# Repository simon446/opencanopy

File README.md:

# OpenCanopy — Tabletop Automated Pepper Grower

Open-source, zero-config, offline-first tabletop grow unit for a single hot pepper plant.

OpenCanopy is an open-hardware project: a compact, living-room-friendly appliance that keeps one hot
pepper plant healthy indoors with minimal user involvement. It combines a broad-spectrum horticultural
LED, automated pump irrigation with soil-moisture sensing, climate/VPD monitoring, water-safety
interlocks, and a simple LED status interface — all driven by deterministic, fully local **Rust**
firmware (`no_std`, `esp-hal`) on an ESP32-S3.

📖 **Docs site:** <https://simon446.github.io/opencanopy/> · 🧩 **Contributing:** [`CONTRIBUTING.md`](CONTRIBUTING.md) · ⚖️ **Licensing:** [`LICENSES/`](LICENSES/)

The project is built **work item by work item**, organized by engineering discipline. The full
engineering plan and the per-discipline work-item breakdown live in [`plan/`](plan/) — the design
source for the build (engineering spec + work items), tracked alongside the implementation in this repo.

## Project status

- **Repository skeleton, licensing, scope lock, risk register, and CI are in place** (the Project &
  Repo track is complete) — every discipline has a home and quality gates run on each PR.
- **Firmware language: Rust** (`no_std` + `esp-hal`), with a host-testable `control` crate and
  `cargo fmt`/`clippy`/`test` gates in CI.
- The remaining discipline tracks (plant science, firmware, electronics, mechanical, validation, docs)
  follow the work-item breakdown in `plan/`. A spec design review (§23) added pre-order modeling and
  bench-characterization gates and an n=2 parallel grow trial.

## Where things live

| What | Path |
|---|---|
| Documentation (rendered) | <https://simon446.github.io/opencanopy/> |
| Documentation (source) | [`docs/`](docs/) — requirements, scope, risk register, guides |
| Contributing & workflow | [`CONTRIBUTING.md`](CONTRIBUTING.md); issue/PR templates in [`.github/`](.github/) |
| Licensing (per asset type) | [`LICENSES/`](LICENSES/) |
| Implementation subtrees | [`firmware/`](firmware/), [`electronics/`](electronics/), [`mechanical/`](mechanical/), [`validation/`](validation/), [`scripts/`](scripts/) |
| Work items & engineering spec (design source) | [`plan/`](plan/) — engineering spec + per-discipline work items |

## Scope

- **In V1:** one plant, fixed hot-pepper profile, dimmable full-spectrum LED with automated schedule,
  substrate moisture sensing, automated pump watering, reservoir-level + leak safety, temp/humidity
  sensing with VPD, circulation fan, 5-LED status interface, local deterministic firmware, and open
  hardware/firmware/CAD with simulation, hardware-in-loop, and grow-trial validation.
- **Not in V1:** camera/AI plant diagnosis, cloud control, automatic pH/EC dosing, multi-plant
  support, required mobile app, or AC mains inside the unit.

See [`docs/scope.md`](docs/scope.md) for the locked non-goals and [`docs/product-requirements.md`](docs/product-requirements.md)
for the locked physical/hardware envelope.

## Repository layout

The standard open-hardware structure is in place; each subtree has a README describing its purpose:

- `firmware/` — Rust workspace: `control/` (host-testable `no_std` logic), `controller/` (`esp-hal`
  binary), `sim/`, `hil/`.
- `electronics/` — KiCad PCB, wiring, BOM, and electrical verification.
- `mechanical/` — CAD/STEP/STL, drawings, and print settings.
- `docs/` — requirements, scope, risk register, and the guides that ship with V1.
- `validation/` — test plans, measurements, and grow-trial records.
- `scripts/` — tooling (`bom_check.py` §16.3 grow-light gate, `stl_check.py`, calculators).

Full layout: spec §14 (in `plan/`).

## Release gate

V1 is tagged only when the acceptance criteria in the V1 spec (§21, in `plan/`) are all met, as proven
by the Validation & QA track — including an **n=2 parallel grow trial** (design-review decision, §23).

## License

Per-asset open-source licensing — **Apache-2.0** firmware/scripts, **CERN-OHL-S v2** hardware/mechanical,
**CC BY 4.0** docs. See [`LICENSES/`](LICENSES/) and its [mapping note](LICENSES/README.md).

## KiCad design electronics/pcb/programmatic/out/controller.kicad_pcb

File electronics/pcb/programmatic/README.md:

<!-- SPDX-License-Identifier: CERN-OHL-S-2.0 -->
# Programmatic PCB — headless code → Gerbers (no KiCad GUI)

A **fully scripted, GUI-free** path from our schematic netlist to a routed board and a fabrication
package, using [**tscircuit**](https://tscircuit.com) (React/TSX EDA with a built-in autorouter and
Gerber export). This answers "can the PCB be built programmatically?" — **yes**, and this directory is
the working proof, generated from [`../netlist/controller_netlist.py`](../netlist/controller_netlist.py).

Built following the official [tscircuit skill](https://github.com/tscircuit/skill) idioms (named-net
connectivity, real passive elements, `pinLabels`).

## Files

| File | What |
|---|---|
| [`gen_tscircuit.py`](gen_tscircuit.py) | Generator: reads the netlist → emits the tscircuit board. |
| `controller.circuit.tsx` | Generated board (60 populated parts, 169 net connections). Do not hand-edit. |
| [`build.sh`](build.sh) | One-shot pipeline: install toolchain → generate → build → export. |
| `out/controller.gerbers.zip` | **Gerbers + drill + BOM + pick-and-place** — a complete fab package. |
| `out/controller.kicad_pcb` | The same board as a KiCad PCB (bridge back to KiCad for refinement). |
| `out/controller.pcb.png` | Rendered preview of the auto-placed/-routed board. |

## Reproduce

```sh
./build.sh          # needs node+npm, bun, network (installs @tscircuit/cli on first run)
```

## The honest status — this is a DRAFT, not a fab-ready board

The pipeline is real and the outputs are genuine fab-format files, but **don't send them to a fab as
is**:

1. **Footprints:** passive footprints (0402/0805/1206/1210/2512) are real; **IC, connector, and the
   ESP32-S3 module footprints are single-row `pinrowN` placeholders** — correct pin *count*, wrong
   land pattern. Swap in real footprints (`tsci search`/`tsci import`, or KiCad libraries) before fab.
2. **Layout quality:** auto-placement + autoroute is **autorouter-grade**. The autorouter logged
   `ran out of iterations` — routing is incomplete/rough. It honours the *netlist* but **not** the
   power/analog separation, copper-pour heatsinks, or star ground in
   [`../../analysis/design-rules.md`](../../analysis/design-rules.md). For a 24 V high-current +
   analog-moisture board, that separation is a correctness/safety concern, not cosmetics.
3. **Scope:** only **populated** controller parts are emitted (DNP options omitted; the status-LED
   board is a separate PCB). Diode anode/cathode and module pinouts on placeholder footprints need a
   review pass.

## Where this fits

This is **the** PCB route ([ECO-002](../../analysis/ECO-002-pcb-toolchain.md); KiCad retired): the
(complete, CI-checked) netlist → tscircuit → autoroute → Gerbers, no GUI. Best for fast, reproducible
drafts and CI; refine footprints/placement, then re-export.

To reach a *fabricable* board the remaining work is real footprints + a reviewed power/analog/thermal
placement per [`design-rules.md`](../../analysis/design-rules.md) — the autorouter doesn't remove that
review. If you'd rather do that refinement in KiCad, `out/controller.kicad_pcb` (and the netlist's
`controller.net`) open the design there — **optional interchange**, not required.

> Toolchain note: tscircuit (npm/bun) is **not** a repo dependency or a CI gate — it's an optional
> build tool installed on demand by `build.sh`. The plain-Python netlist ERC remains the committed gate.

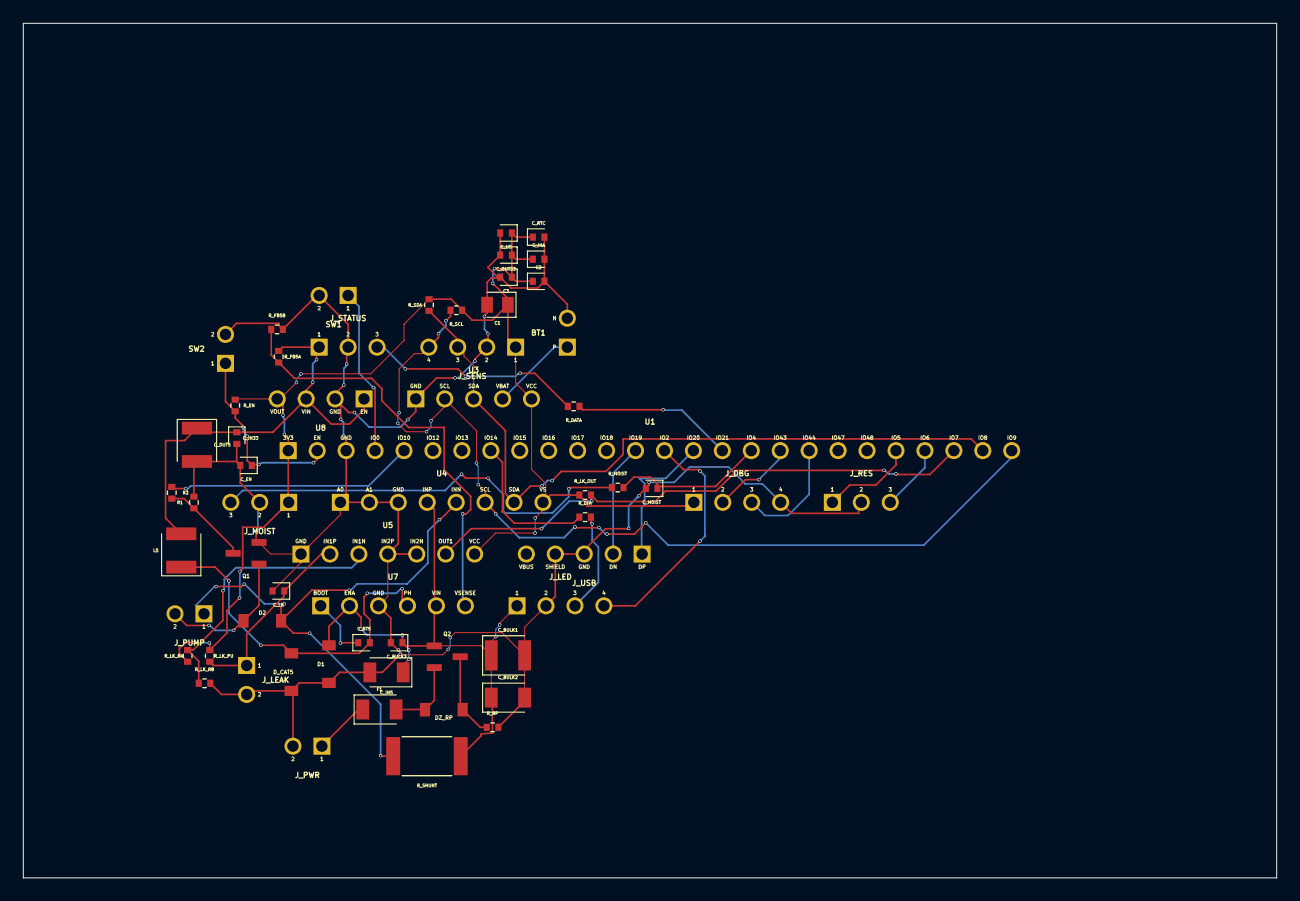
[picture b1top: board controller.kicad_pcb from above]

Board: 2 copper layers, 110.0 x 75.0 mm, 60 parts (0 on the bottom side), 35 nets.

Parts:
BT1: chip_pinrow2
C1: 22uF; capacitor_0805
C2, C3: 100nF; capacitor_0402
C_BT5: 10nF; capacitor_0402
C_BULK1: 100uF; capacitor_1210
C_BULK2: 10uF; capacitor_1206
C_BULK3: 100nF; capacitor_0402
C_EN: 100nF; capacitor_0402
C_IN5: 10uF; capacitor_1206
C_IN33: 1uF; capacitor_0402
C_INA: 100nF; capacitor_0402
C_LK: 100nF; capacitor_0402
C_MOIST: 10nF; capacitor_0402
C_OUT5: 22uF; capacitor_1210
C_OUT33: 1uF; capacitor_0402
C_RTC: 100nF; capacitor_0402
C_U5: 100nF; capacitor_0402
D1, D2: D; diode_sod123
DZ_RP: D; diode_sod123
D_CAT5: D; diode_sod123
F1: F1; fuse_1206
J_DBG: chip_pinrow4
J_LEAK: chip_pinrow2
J_LED: chip_pinrow4
J_MOIST: chip_pinrow3
J_PUMP: chip_pinrow2
J_PWR: chip_pinrow2
J_RES: chip_pinrow3
J_SENS: chip_pinrow4
J_STATUS: chip_pinrow3
J_USB: chip_pinrow5
L5: 10H; inductor_1210
Q1: Q1; mosfet_sot23
Q2: Q2; mosfet_sot23
R1: 10kΩ; resistor_res0402
R2: 100Ω; resistor_res0402
R_DATA: 330Ω; resistor_res0402
R_DIM: 100Ω; resistor_res0402
R_EN: 10kΩ; resistor_res0402
R_FB5A: 22kΩ; resistor_res0402
R_FB5B: 7.15kΩ; resistor_res0402
R_LK_OUT: 10kΩ; resistor_res0402
R_LK_PU: 100kΩ; resistor_res0402
R_LK_RA: 10kΩ; resistor_res0402
R_LK_RB: 10kΩ; resistor_res0402
R_MOIST: 1kΩ; resistor_res0402
R_RP: 100kΩ; resistor_res0402
R_SCL: 4.7kΩ; resistor_res0402
R_SDA: 4.7kΩ; resistor_res0402
R_SHUNT: 100mΩ; resistor_res2512
SW1, SW2: chip_pinrow2
U1: chip_pinrow26
U3: chip_pinrow5
U4: chip_pinrow8
U5: chip_pinrow7
U7: chip_pinrow6
U8: chip_pinrow4

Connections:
BOOT5: C_BT5.1, U7.1
EN: C_EN.1, R_EN.2, SW2.1, U1.2
FB5: R_FB5A.2, R_FB5B.1, U7.6
GND: BT1.2, C1.2, C2.2, C3.2, C_BULK1.2, C_BULK2.2, C_BULK3.2, C_EN.2, C_IN5.2, C_IN33.2, C_INA.2, C_LK.2, C_MOIST.2, C_OUT5.2, C_OUT33.2, C_RTC.2, C_U5.2, D1.1, D_CAT5.1, J_DBG.4, J_LEAK.2, J_LED.2, J_MOIST.2, J_PWR.2, J_RES.2, J_SENS.2, J_STATUS.2, J_USB.3, J_USB.4, Q1.2, R1.2, R_FB5B.2, R_LK_RB.2, R_RP.2, SW1.2, SW2.2, U1.3, U3.1, U4.1, U4.2, U4.3, U5.1, U5.4, U5.5, U7.3, U8.2
IO0_BOOT: SW1.1, U1.4
LEAK_DET: R_LK_OUT.2, U1.24, U5.6
LEAK_REF: R_LK_RA.2, R_LK_RB.1, U5.3
LEAK_SENSE: C_LK.1, J_LEAK.1, R_LK_PU.2, U5.2
LED_DIM: R_DIM.1, U1.8
LED_DIM_OUT: J_LED.3, R_DIM.2
LED_NTC: J_LED.4, U1.14
MOIST_ADC: C_MOIST.1, R_MOIST.2, U1.17
MOIST_SIG: J_MOIST.3, R_MOIST.1
P3V3: C1.1, C2.1, C3.1, C_INA.1, C_OUT33.1, C_RTC.1, C_U5.1, J_DBG.1, J_MOIST.1, J_SENS.1, R_EN.1, R_LK_OUT.1, R_LK_PU.1, R_LK_RA.1, R_SCL.1, R_SDA.1, U1.1, U3.5, U4.8, U5.7, U8.4
P5V: C_IN33.1, C_OUT5.1, J_STATUS.1, L5.2, R_FB5A.1, U8.1, U8.3
P24V: C_BULK1.1, C_BULK2.1, C_BULK3.1, C_IN5.1, D1.2, J_LED.1, Q2.1, R_SHUNT.1, U4.4, U7.2, U7.5
P24V_FUSED: DZ_RP.2, F1.2, Q2.2
P24V_IN: F1.1, J_PWR.1
PH5: C_BT5.2, D_CAT5.2, L5.1, U7.4
PUMP_GATE: Q1.3, R1.1, R2.2
PUMP_P: D2.2, J_PUMP.1, R_SHUNT.2, U4.5
PUMP_PWM: R2.1, U1.5
PUMP_RET: D2.1, J_PUMP.2, Q1.1
RES_LEVEL_ADC: J_RES.3, U1.23
RES_LOW_SW: J_RES.1, U1.22
RP_GATE: DZ_RP.1, Q2.3, R_RP.1
SCL: J_SENS.4, R_SCL.2, U1.26, U3.2, U4.6
SDA: J_SENS.3, R_SDA.2, U1.25, U3.3, U4.7
STATUS_DATA: R_DATA.1, U1.16
STATUS_DATA_OUT: J_STATUS.3, R_DATA.2
UART_RX: J_DBG.3, U1.19
UART_TX: J_DBG.2, U1.18
USB_DM: J_USB.2, U1.13
USB_DP: J_USB.1, U1.15
VBAT: BT1.1, U3.4
